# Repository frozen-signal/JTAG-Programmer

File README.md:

# Description

A Kicad project for a JTAG Programmer. Compatible with Lattice Diamond Programmer, Radiant Programmer and iCEcube2.

# How to use

## One-time setup

Once assembled, a one-time setup need to be done:
1. Download and install [FT_Prog from FTDI](https://ftdichip.com/utilities/#ft_prog)
1. Connect the JTAG-Programmer to your PC with a USB cable.
1. Do a scan: DEVICE > Scan and parse.<br />
1. Go to FILE > Open Template and select "JTAG_PROGRAMMER.xml".<br />
1. Go to DEVICE > Program, and click "Erase". Once completed, click "Program".<br />
1. Make sure the JTAG-Programmer has been correctly programmed by quitting FT_Prog and re-opening it, then doing a scan again. Check that the template has been applied to the JTAG-Programmer ("Product Desc" should be "JTAG Program").

## Example of Programming a MACHXO2 FPGA with Lattice Diamond Programmer

This shows an example of how the JTAG-Programmer can be used to program a FPGA. This example suppose you already have installed the Lattice Diamond Programmer (As standalone or as part of the [Lattice Diamond Toolchain](https://www.latticesemi.com/Products/DesignSoftwareAndIP/FPGAandLDS/LatticeDiamond)
1. Make sure the JTAG-Programmer is connected to the PC.
1. Run the Lattice Diamond Programmer, select "Create a new blank project" is selected, and click "OK".<br />
1. Click on the "Generic JTAG Device" under Device Family, and select the FPGA family.<br />
1. Click on the element under "Device" and select the correct device.<br />
1. Make sure the Operation is "Flash Erase,Program,Verify".
1. Under File Name, select the programming file. In our case, it's the generated JEDEC file (*.jed).
1. Connect the JTAG cable to the device and click "Program".<br />
1. Once Diamond Programmer finishes, your FPGA should now be programmed.

# An overview of the JTAG-Programmer
(TODO: Add a description of the pins)

<p><i>A rendering of the programmer</i></p>

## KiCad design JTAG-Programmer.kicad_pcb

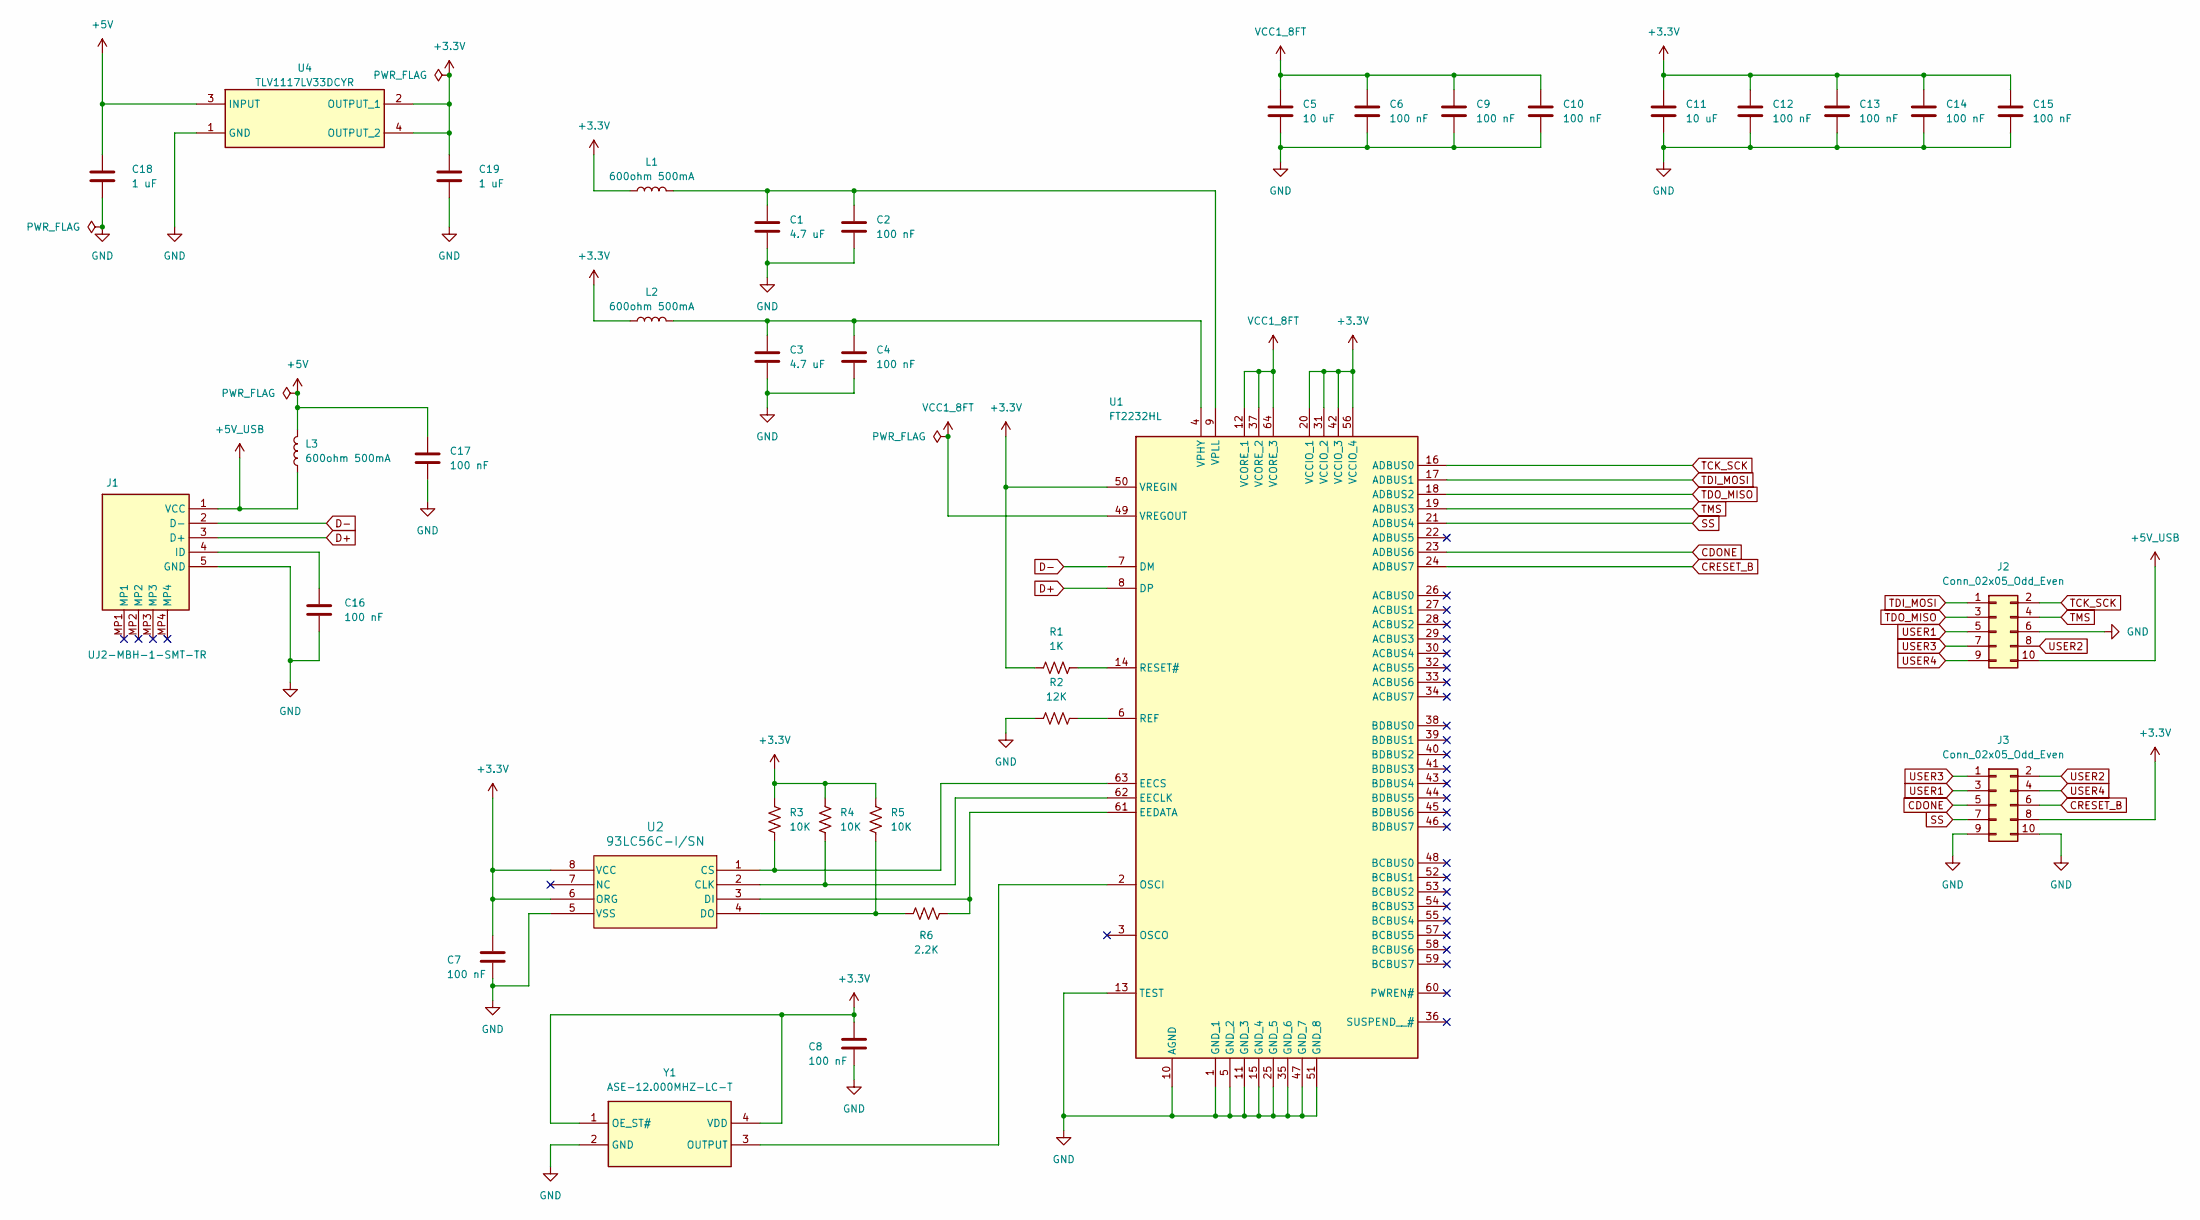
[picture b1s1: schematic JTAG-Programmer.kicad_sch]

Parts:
C1, C3: 4.7 uF; C_0603_1608Metric
C2, C4, C6, C7, C8, C9, C10, C12, C13, C14, C15, C16, C17: 100 nF; C_0402_1005Metric
C5, C11: 10 uF; C_0603_1608Metric
C18, C19: 1 uF; C_0603_1608Metric
J1: UJ2-MBH-1-SMT-TR; UJ2MBH1SMTTR; Mouser Part Number 490-UJ2-MBH-1-SMT
J2, J3: Conn_02x05_Odd_Even; PinHeader_2x05_P2.54mm_Vertical
L1, L2, L3: 600ohm 500mA; L_0603_1608Metric
R1: 1K; R_0402_1005Metric
R2: 12K; R_0402_1005Metric
R3, R4, R5: 10K; R_0402_1005Metric
R6: 2.2K; R_0402_1005Metric
U1: FT2232HL; QFP50P1200X1200X160-64N; Mouser Part Number 895-FT2232HL
U2: 93LC56C-I/SN; SOIC8-N_MC_MCH
U4: TLV1117LV33DCYR; SOT230P700X180-4N; Mouser Part Number 595-TLV1117LV33DCYR
Y1: ASE-12.000MHZ-LC-T; ASE24576MHZLCT; Mouser Part Number 815-ASE12.000MHZLCT

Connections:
+3.3V: C7.1, C8.1, C11.1, C12.1, C13.1, C14.1, C15.1, C19.1, J3.8, L1.1, L2.1, R1.1, R3.2, R4.2, R5.2, U1.20 (VCCIO_1), U1.31 (VCCIO_2), U1.42 (VCCIO_3), U1.50 (VREGIN), U1.56 (VCCIO_4), U2.6 (ORG), U2.8 (VCC), U4.2 (OUTPUT_1), U4.4 (OUTPUT_2), Y1.1 (OE_ST#), Y1.4 (VDD)
+5V: C17.1, C18.1, L3.2, U4.3 (INPUT)
+5V_USB: J1.1 (VCC), J2.10, L3.1
CDONE: J3.5, U1.23 (ADBUS6)
CRESET_B: J3.6, U1.24 (ADBUS7)
D+: J1.3 (D+), U1.8 (DP)
D-: J1.2 (D-), U1.7 (DM)
GND: C1.2, C2.2, C3.2, C4.2, C5.2, C6.2, C7.2, C8.2, C9.2, C10.2, C11.2, C12.2, C13.2, C14.2, C15.2, C16.2, C17.2, C18.2, C19.2, J1.5 (GND), J2.6, J3.9, J3.10, R2.1, U1.1 (GND_1), U1.5 (GND_2), U1.10 (AGND), U1.11 (GND_3), U1.13 (TEST), U1.15 (GND_4), U1.25 (GND_5), U1.35 (GND_6), U1.47 (GND_7), U1.51 (GND_8), U2.5 (VSS), U4.1 (GND), Y1.2 (GND)
unnamed: C16.1, J1.4 (ID)
unnamed: R4.1, U1.62 (EECLK), U2.2 (CLK)
unnamed: R3.1, U1.63 (EECS), U2.1 (CS)
unnamed: R6.1, U1.61 (EEDATA), U2.3 (DI)
unnamed: U1.2 (OSCI), Y1.3 (OUTPUT)
unnamed: R2.2, U1.6 (REF)
unnamed: R1.2, U1.14 (RESET#)
unnamed: C3.1, C4.1, L2.2, U1.4 (VPHY)
unnamed: C1.1, C2.1, L1.2, U1.9 (VPLL)
unnamed: R5.1, R6.2, U2.4 (DO)
SS: J3.7, U1.21 (ADBUS4)
TCK_SCK: J2.2, U1.16 (ADBUS0)
TDI_MOSI: J2.1, U1.17 (ADBUS1)
TDO_MISO: J2.3, U1.18 (ADBUS2)
TMS: J2.4, U1.19 (ADBUS3)
USER1: J2.5, J3.3
USER2: J2.8, J3.2
USER3: J2.7, J3.1
USER4: J2.9, J3.4
VCC1_8FT: C5.1, C6.1, C9.1, C10.1, U1.12 (VCORE_1), U1.37 (VCORE_2), U1.49 (VREGOUT), U1.64 (VCORE_3)

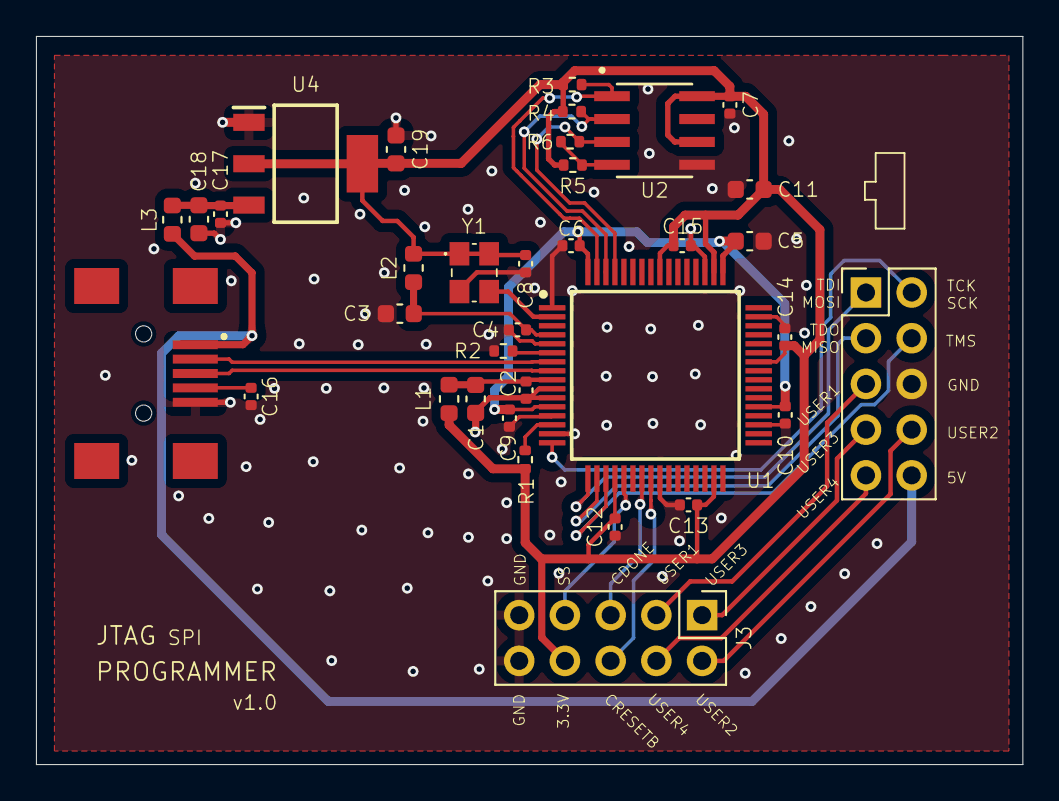
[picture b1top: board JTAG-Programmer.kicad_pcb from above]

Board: 2 copper layers, 54.8 x 40.5 mm, 35 parts (0 on the bottom side), 28 nets.

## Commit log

2025-05-23 Small changes & added a readme
2025-05-27 Minimalistic How-To
2025-05-27 Added minimalistic how-to (#1)
2025-06-20 Added missing JTAG_PROGRAMMER.xml
